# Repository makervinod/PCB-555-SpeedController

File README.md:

# 555 Speed Controller

## A 555 Timer-based Speed Controller for controlling DC Speed/Dimming

<br>

> This speed controller was purposely built for controlling the speed of Ender 3D Printer's Hotend Cooling Fan to help the hot-end support unofficial cooling fans. But it can be used for other purposes too! ( No limits to your use case! )

---

### Specifications:

- Operating Voltage: **12V to 24V**
- Maximum Output Current: **0.5 Amp (customizable)**

---

### Components Required:

| Sr. No. | Part Number/Name | Package  | Quantity | Description               |
| ------- | ---------------- | -------- | :------: | ------------------------- |
| 1       | NE555            | SOIC-8   |    1     | 555-Timer IC              |
| 2       | 1N4742           | DO-41    |    1     | Diode (12V Zener, 1 Watt) |
| 3       | LL4148 (1N4148)  | MiniMELF |    2     | Diode                     |
| 4       | S8050 (J3Y)      | SOT-23   |    1     | NPN Transistor            |
| 5       | 22uF 50V         | 1210     |    1     | Ceramic Capacitor         |
| 6       | 0.1uF 16V        | 0805     |    1     | Ceramic Capacitor         |
| 7       | 0.01uF 16V       | 0805     |    1     | Ceramic Capacitor         |
| 8       | 560 Ω            | 2512     |    2     | Resistor                  |
| 9       | 10 kΩ            | 0805     |    1     | Resistor                  |
| 10      | 1 kΩ             | 0805     |    1     | Resistor                  |
| 11      | 4.7 kΩ           | 0805     |    1     | Resistor                  |
| 12      | 10 kΩ            | Preset   |    1     | Preset Potentiomenter     |
| 13      | LED (Any color)  | 0805     |    1     | LED                       |

---

### Fabrication Notes:

1. This was built using the PCB Toner transfer process at home.
2. Use the `print` feature of KiCAD to print the PCB design according to your requirements.
3. I tinned the board using some normal solder wire & flux (budget-friendly)
4. Refer to the schematic to relate the placement of the components.

---

### Additional Notes:

> The circuit will dissipate high heat if operated beyond the specified rating. Choose an appropriate combination of the Zener diode & the heat-dissipating resistors to satisfy your requirements.

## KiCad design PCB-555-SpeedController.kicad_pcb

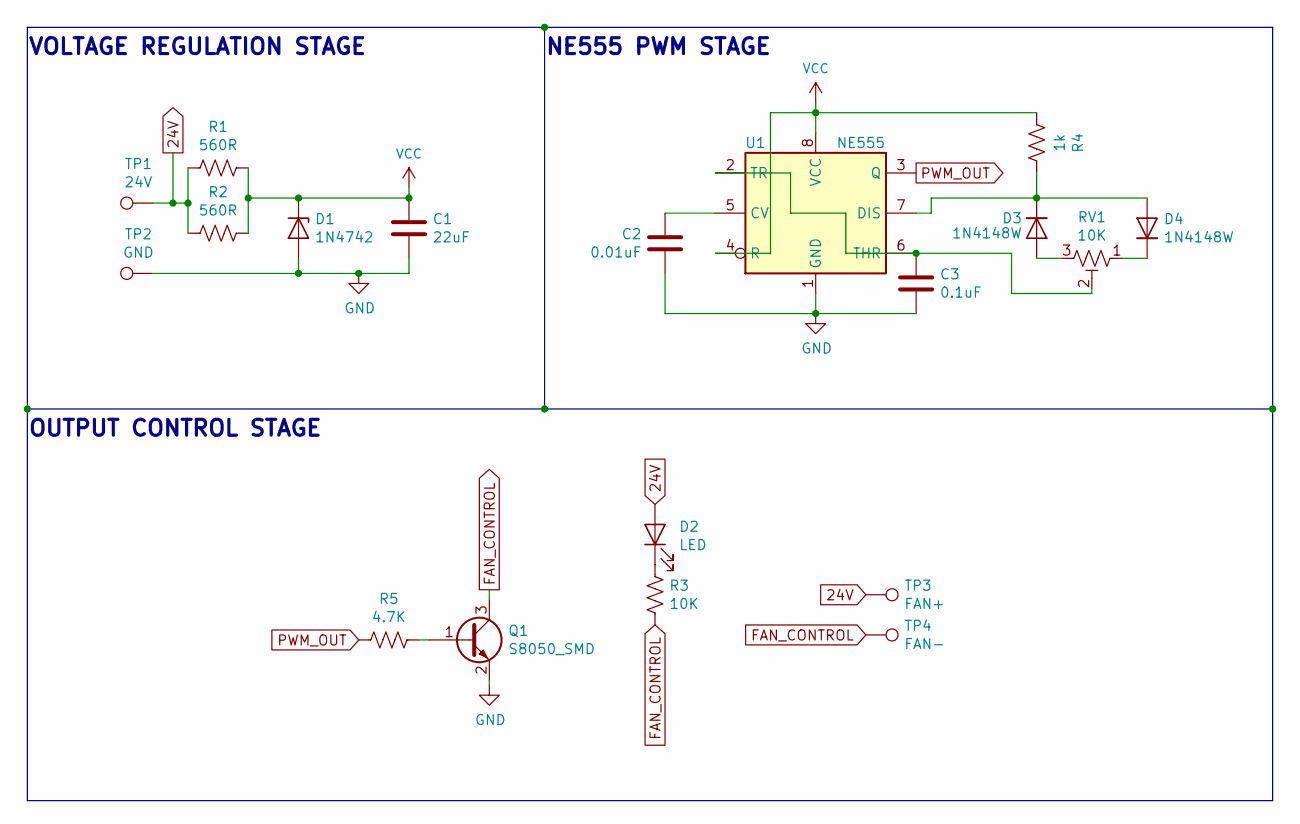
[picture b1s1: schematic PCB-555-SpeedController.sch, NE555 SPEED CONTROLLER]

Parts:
C1: 22uF; C_1210_3225Metric
C2: 0.01uF; C_0805_2012Metric
C3: 0.1uF; C_0805_2012Metric
D1: 1N4742; D_DO-41_SOD81_P10.16mm_Horizontal
D2: LED; LED_0805_2012Metric
D3, D4: 1N4148W; D_MiniMELF
Q1: S8050_SMD; SOT-23
R1, R2: 560R; R_2512_6332Metric
R3: 10K; R_0805_2012Metric
R4: 1k; R_0805_2012Metric
R5: 4.7K; R_0805_2012Metric
RV1: 10K; Potentiometer_Piher_PT-6-V_Vertical
TP1: 24V; TestPoint_Pad_2.0x2.0mm
TP2: GND; TestPoint_Pad_2.0x2.0mm
TP3: FAN+; TestPoint_Pad_2.0x2.0mm
TP4: FAN-; TestPoint_Pad_2.0x2.0mm
U1: NE555; SOIC-8_3.9x4.9mm_P1.27mm

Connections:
24V: D2.2 (A), R1.2, R2.2, TP1.1, TP3.1
FAN_CONTROL: Q1.3 (C), R3.1, TP4.1
GND: C1.2, C2.1, C3.2, D1.2 (A), Q1.2 (E), TP2.1, U1.1 (GND)
unnamed: C2.2, U1.5 (CV)
unnamed: C3.1, RV1.2, U1.2 (TR), U1.6 (THR)
unnamed: D2.1 (K), R3.2
unnamed: D3.1 (K), D4.2 (A), R4.1, U1.7 (DIS)
unnamed: D3.2 (A), RV1.3
unnamed: D4.1 (K), RV1.1
unnamed: Q1.1 (B), R5.1
PWM_OUT: R5.2, U1.3 (Q)
VCC: C1.1, D1.1 (K), R1.1, R2.1, R4.2, U1.4 (R), U1.8 (VCC)

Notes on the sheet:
OUTPUT CONTROL STAGE
NE555 PWM STAGE
VOLTAGE REGULATION STAGE

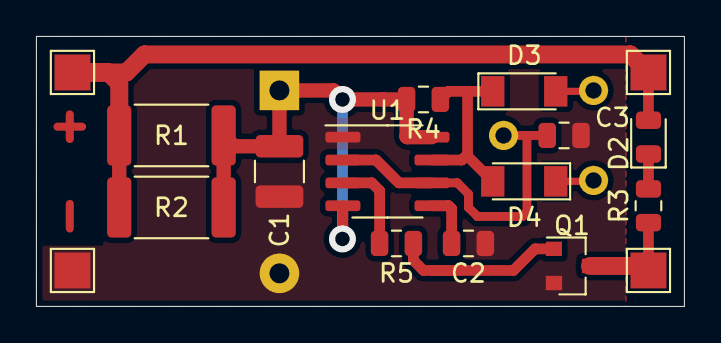
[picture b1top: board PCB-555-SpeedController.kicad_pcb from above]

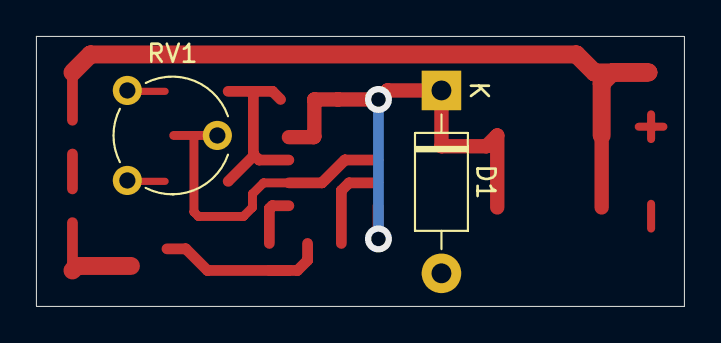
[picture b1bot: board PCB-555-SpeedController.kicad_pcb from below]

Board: 2 copper layers, 36.0 x 15.0 mm, 19 parts (2 on the bottom side), 12 nets.

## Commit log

2022-04-22 Finished formatting the design
